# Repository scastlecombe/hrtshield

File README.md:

hrtshield
=========

Arduino HART shield Eagle circuit and PCB

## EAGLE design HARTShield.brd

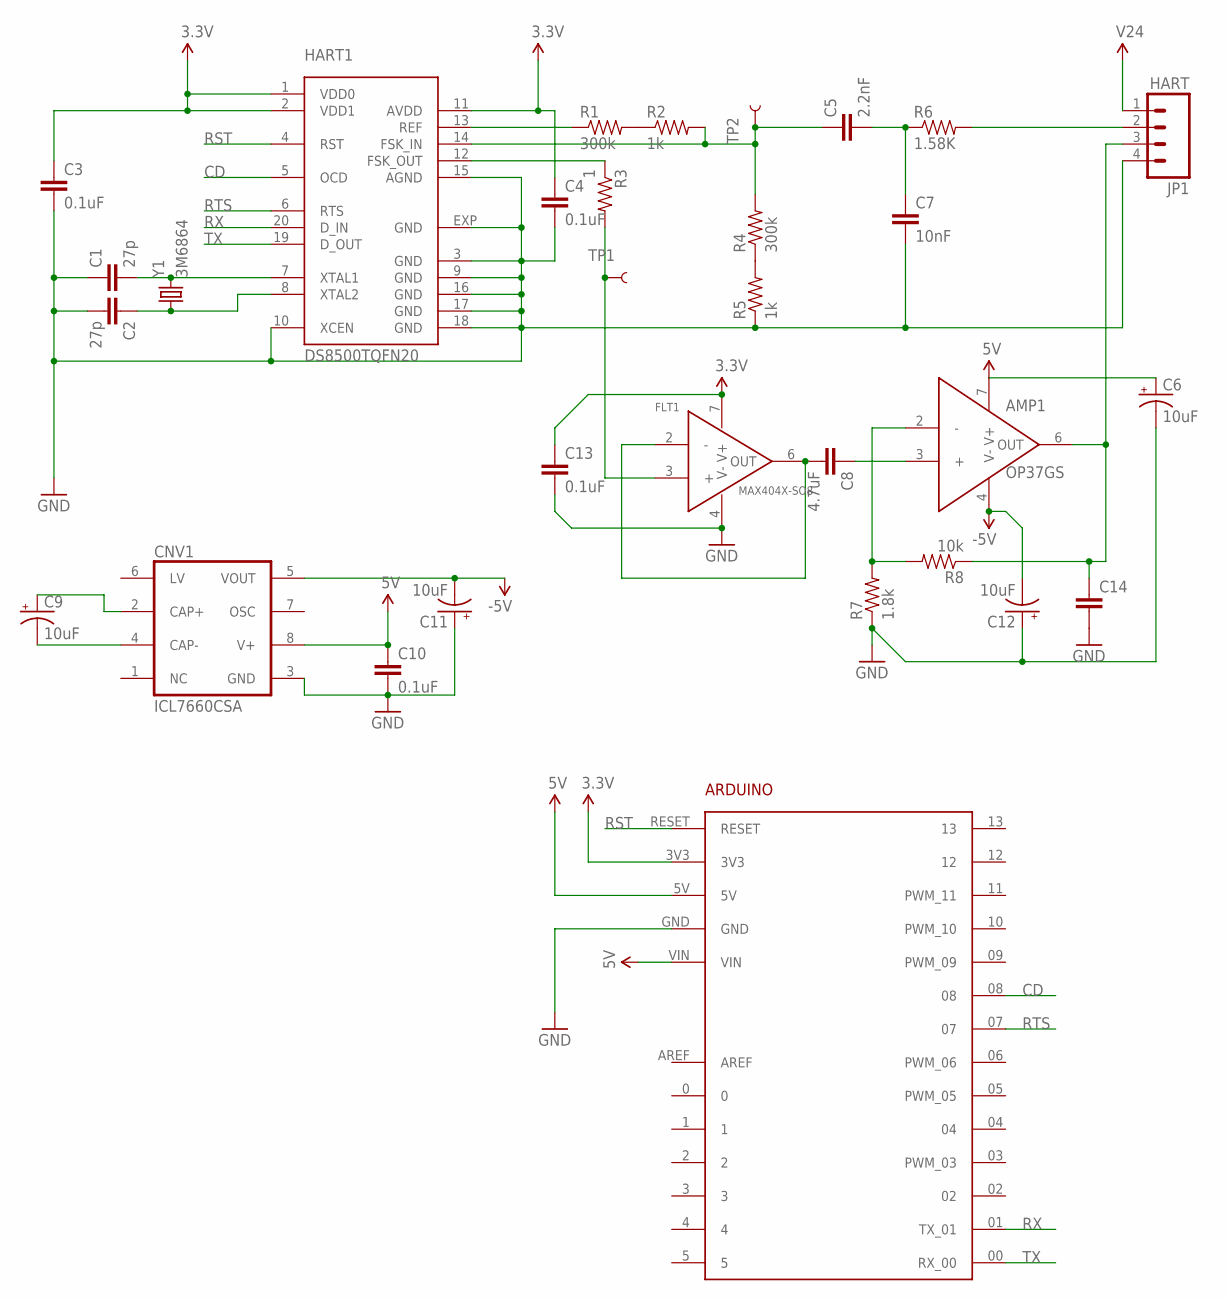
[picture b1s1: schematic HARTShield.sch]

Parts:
AMP1: OP37GS; SO8
ARDUINO1: ARDUINO
C1, C2: 27p; 0603-CAP
C3, C4, C10: 0.1uF; 0603-CAP
C5: 2.2nF; 0603-CAP
C6, C9, C11, C12: 10uF; EIA3216
C7: 10nF; 0603-CAP
C8: 4.7uF; 0603-CAP
C13: 0.1uF; CAP-PTH-SMALL-KIT
C14: 0.1UF-50V-20%(PTH)KIT-EZ; CAP-PTH-SMALL-KIT
CNV1: ICL7660CSA; SO08
FLT1: MAX404X-SO8; SO8
HART1: DS8500TQFN20; TQFN20-5X5
JP1: HART; SCREWTERMINAL-3.5MM-4
R1, R4: 300k; 0805
R2, R5: 1k; 0805
R3: 1; 1206
R6: 1.58K; 0603-RES
R7: 1.8k; 0805
R8: 10k; 0805
TP1, TP2: TEST-POINT2; PAD.02X.02
Y1: 3M6864; HC49UP

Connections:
3.3V: ARDUINO1.3V3, C3.1, C4.1, C13.1, FLT1.7 (V+), HART1.1 (VDD0), HART1.2 (VDD1), HART1.11 (AVDD)
5V: AMP1.7 (V+), ARDUINO1.5V, ARDUINO1.VIN, C6.A (+), C10.1, CNV1.8 (V+)
CD: ARDUINO1.08, HART1.5 (OCD)
GND: ARDUINO1.GND, C1.1, C2.2, C3.2, C4.2, C6.C (-), C7.2, C10.2, C11.A (+), C12.A (+), C13.2, C14.2, CNV1.3 (GND), FLT1.4 (V-), HART1.3 (GND), HART1.9 (GND), HART1.10 (XCEN), HART1.15 (AGND), HART1.16 (GND), HART1.17 (GND), HART1.18 (GND), HART1.EXP (GND), JP1.4, R5.1, R7.1
unnamed: C2.1, HART1.8 (XTAL2), Y1.1
unnamed: C1.2, HART1.7 (XTAL1), Y1.2
unnamed: R1.2, R2.1
unnamed: HART1.13 (REF), R1.1
unnamed: FLT1.3 (+), R3.2, TP1.P$1
unnamed: AMP1.3 (+), C8.1
unnamed: R4.1, R5.2
unnamed: C5.1, HART1.14 (FSK_IN), R2.2, R4.2, TP2.P$1
unnamed: C5.2, C7.1, R6.1
unnamed: C8.2, FLT1.2 (-), FLT1.6 (OUT)
unnamed: JP1.2, R6.2
unnamed: AMP1.6 (OUT), C14.1, JP1.3, R8.1
unnamed: AMP1.2 (-), R7.2, R8.2
unnamed: HART1.12 (FSK_OUT), R3.1
unnamed: C9.C (-), CNV1.4 (CAP-)
unnamed: C9.A (+), CNV1.2 (CAP+)
RST: ARDUINO1.RESET, HART1.4 (RST)
RTS: ARDUINO1.07, HART1.6 (RTS)
RX: ARDUINO1.01 (TX_01), HART1.20 (D_IN)
TX: ARDUINO1.00 (RX_00), HART1.19 (D_OUT)
VCC: JP1.1
VNEG: AMP1.4 (V-), C11.C (-), C12.C (-), CNV1.5 (VOUT)

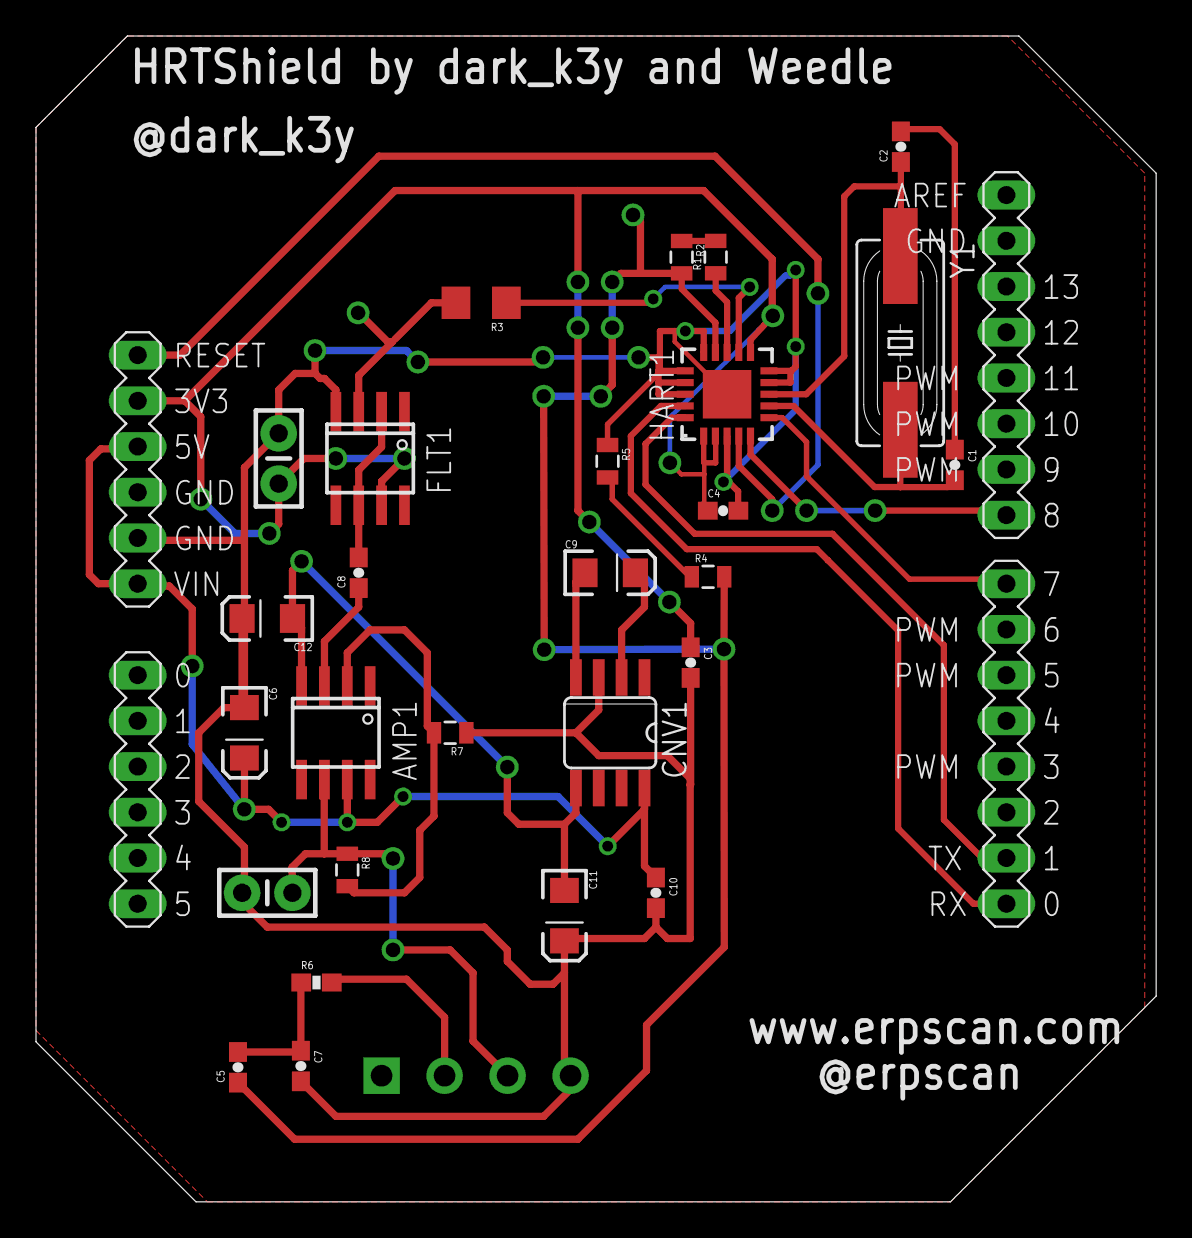
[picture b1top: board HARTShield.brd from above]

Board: 2 copper layers, 62.2 x 64.8 mm, 31 parts (1 on the bottom side), 25 nets.

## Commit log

2013-11-05 Initial revision.
2013-11-05 Added circuit pdf and fixed parts list.
2013-11-05 Fixed parts list.
2014-01-21 Minor fixes on partlist.
2014-01-21 Fixed partlists and label.

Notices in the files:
parts and their libraries:
SparkFun-FreqCtrl: Licensing: CC v3.0 Share-Alike You are welcome to use this library for commercial purposes.
